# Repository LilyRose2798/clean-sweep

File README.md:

# Clean Sweep

A remix of the [Sweep](https://github.com/davidphilipbarr/Sweep) (based on the original [Ferris](https://github.com/pierrechevalier83/ferris)) that has a tweaked shape and aims to have a cleaner looking design (in particular the layout of the traces).

There are 8 total variations, with each possible combination of the following options:
- Face up or face down MCU (uses Pro Micro or clone with same pinout)
- Straight or rounded traces
- Traces primarily on the front or back of the pcb

All designs include just the left half and are reversible, but keep in mind that reversing the pcb also means the traces will be on the opposite side and the MCU will have to be flipped over, so if you wanted to have both a left and right side with front traces and a face down MCU, then you'd need to make both the face down MCU / back traces version and a face up MCU / front traces version (that you would then flip over to use for the right half).

## Images

### Face Down MCU / Rounded Back Traces - Front View

### Face Down MCU / Rounded Back Traces - Back View

### Face Down MCU / Straight Back Traces - Front View

### Face Down MCU / Straight Back Traces - Back View

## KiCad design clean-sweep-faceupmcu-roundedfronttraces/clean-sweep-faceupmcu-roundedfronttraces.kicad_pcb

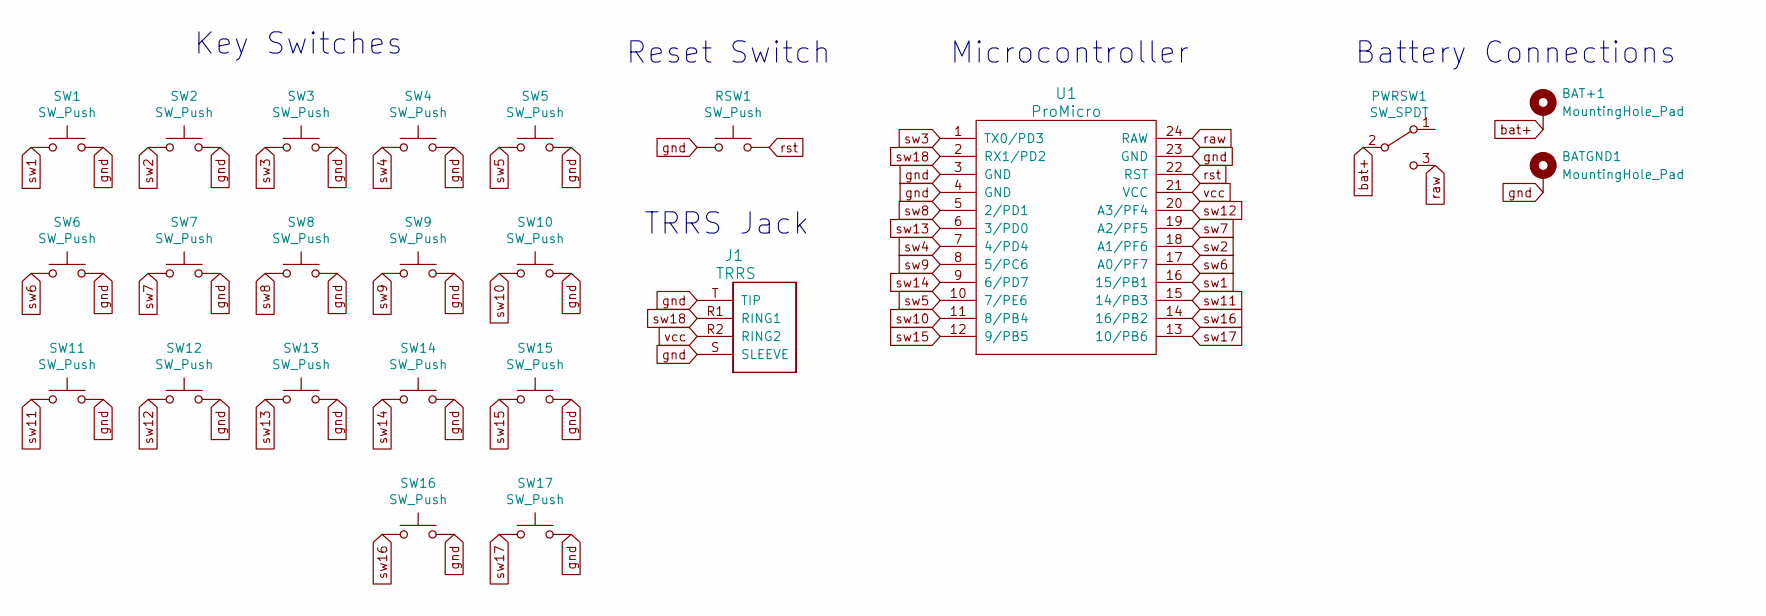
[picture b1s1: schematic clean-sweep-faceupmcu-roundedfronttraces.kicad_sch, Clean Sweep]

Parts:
BAT+1: MountingHole_Pad; VIA-1.4mm
BATGND1: MountingHole_Pad; VIA-1.4mm
J1: TRRS; TRRS-PJ-320A-reversible
PWRSW1: SW_SPDT; SW_SPDT_MSK-12C02-reversible
RSW1: SW_Push; SW_SPST_B3U-1000P-reversible
SW1, SW2, SW3, SW4, SW5, SW6, SW7, SW8, SW9, SW10, SW11, SW12, SW13, SW14, SW15, SW16, SW17: SW_Push; Kailh-PG1350-1u-reversible
U1: ProMicro

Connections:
bat+: BAT+1.1, PWRSW1.2 (B)
gnd: BATGND1.1, J1.S (SLEEVE), J1.T (TIP), RSW1.1, SW1.2, SW2.2, SW3.2, SW4.2, SW5.2, SW6.2, SW7.2, SW8.2, SW9.2, SW10.2, SW11.2, SW12.2, SW13.2, SW14.2, SW15.2, SW16.2, SW17.2, U1.3 (GND), U1.4 (GND), U1.23 (GND)
raw: PWRSW1.3 (C), U1.24 (RAW)
rst: RSW1.2, U1.22 (RST)
sw1: SW1.1, U1.16 (15/PB1)
sw2: SW2.1, U1.18 (A1/PF6)
sw3: SW3.1, U1.1 (TX0/PD3)
sw4: SW4.1, U1.7 (4/PD4)
sw5: SW5.1, U1.10 (7/PE6)
sw6: SW6.1, U1.17 (A0/PF7)
sw7: SW7.1, U1.19 (A2/PF5)
sw8: SW8.1, U1.5 (2/PD1)
sw9: SW9.1, U1.8 (5/PC6)
sw10: SW10.1, U1.11 (8/PB4)
sw11: SW11.1, U1.15 (14/PB3)
sw12: SW12.1, U1.20 (A3/PF4)
sw13: SW13.1, U1.6 (3/PD0)
sw14: SW14.1, U1.9 (6/PD7)
sw15: SW15.1, U1.12 (9/PB5)
sw16: SW16.1, U1.14 (16/PB2)
sw17: SW17.1, U1.13 (10/PB6)
sw18: J1.R1 (RING1), U1.2 (RX1/PD2)
vcc: J1.R2 (RING2), U1.21 (VCC)

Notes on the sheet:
TRRS Jack
Battery Connections
Key Switches
Reset Switch
Microcontroller

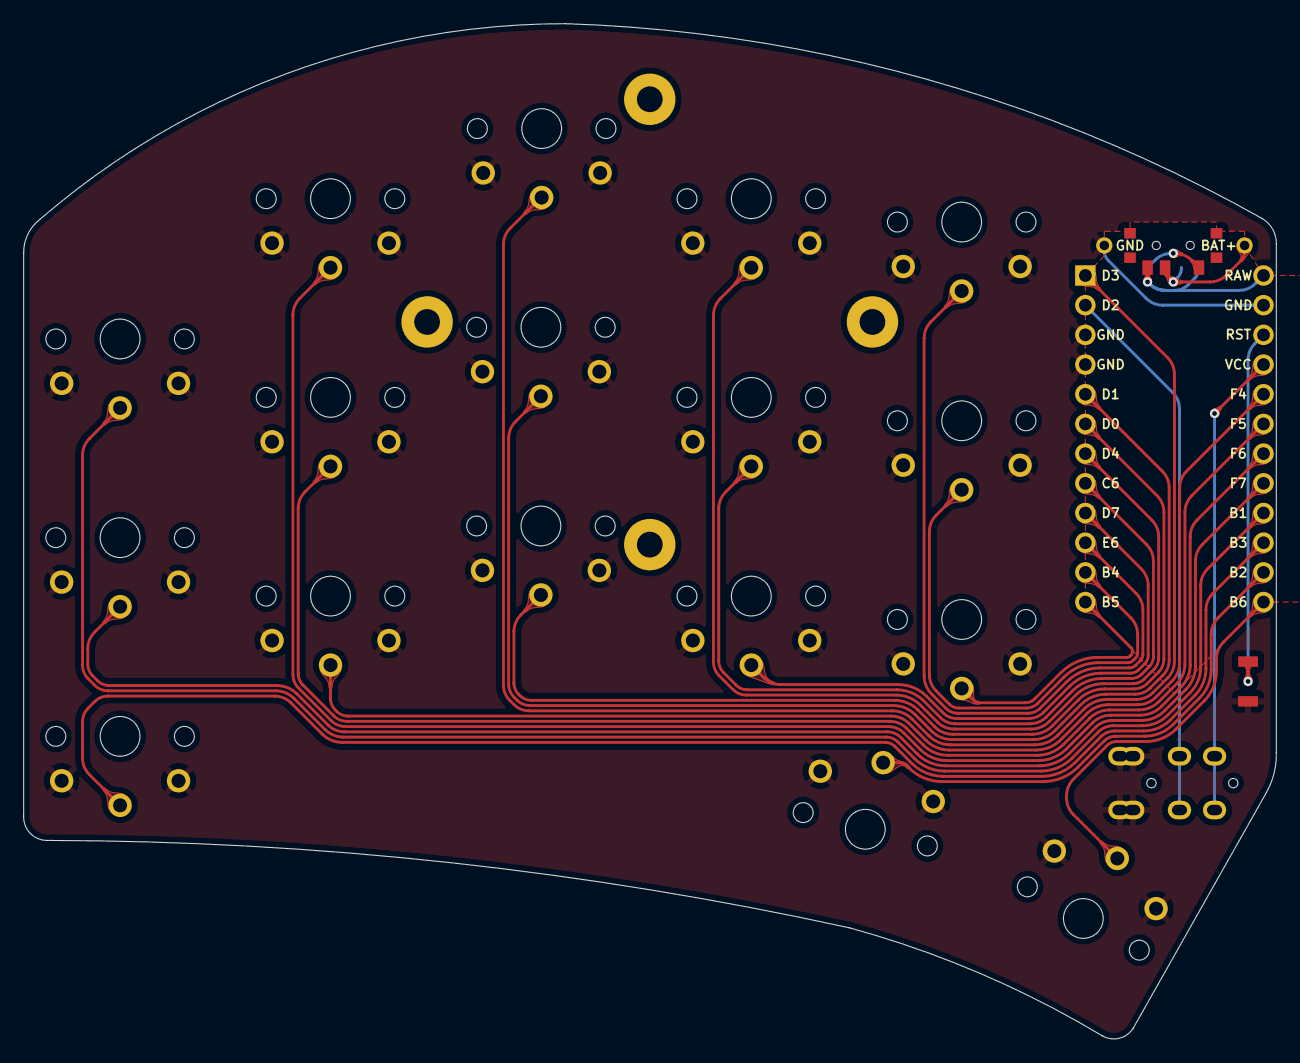
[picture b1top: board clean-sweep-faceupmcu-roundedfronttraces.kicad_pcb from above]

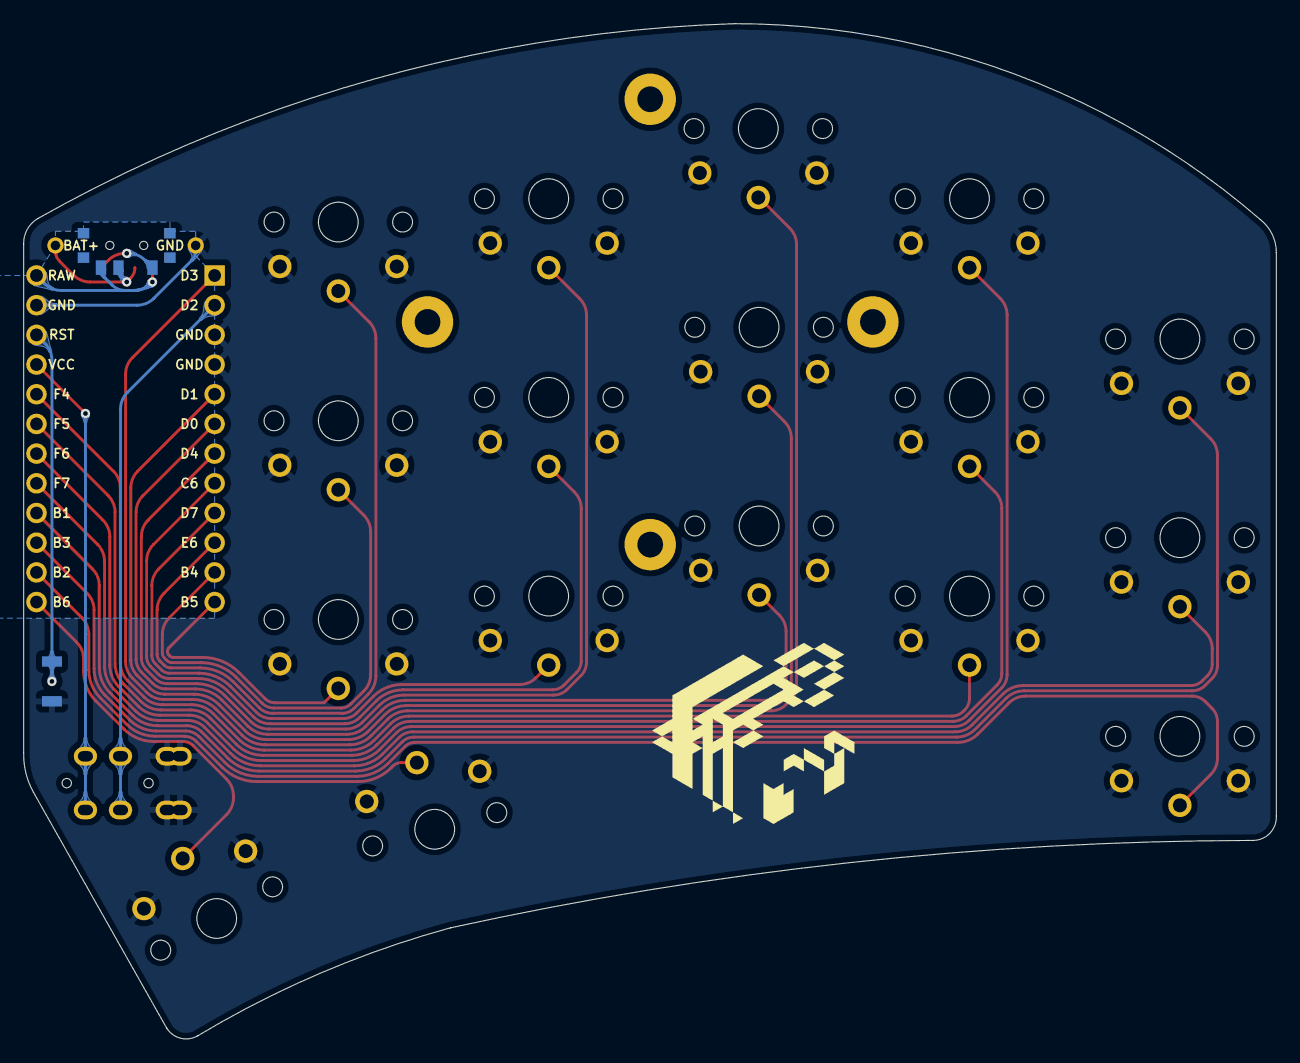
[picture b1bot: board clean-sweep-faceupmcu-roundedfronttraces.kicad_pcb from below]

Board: 2 copper layers, 107.2 x 86.9 mm, 25 parts (3 on the bottom side), 23 nets.

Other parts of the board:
Bee: G*****; Bee-flipped
TP1: Tenting Puck; TentingPuck

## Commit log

2022-03-26 Add silkscreen labels to battery connection pads
2022-03-26 Add images
2022-03-26 Update README to include images and fix caps
2022-03-26 Update gitignore
2022-03-26 Update ground fill
2022-03-26 Update plot config
2022-03-26 Add gerber plots
